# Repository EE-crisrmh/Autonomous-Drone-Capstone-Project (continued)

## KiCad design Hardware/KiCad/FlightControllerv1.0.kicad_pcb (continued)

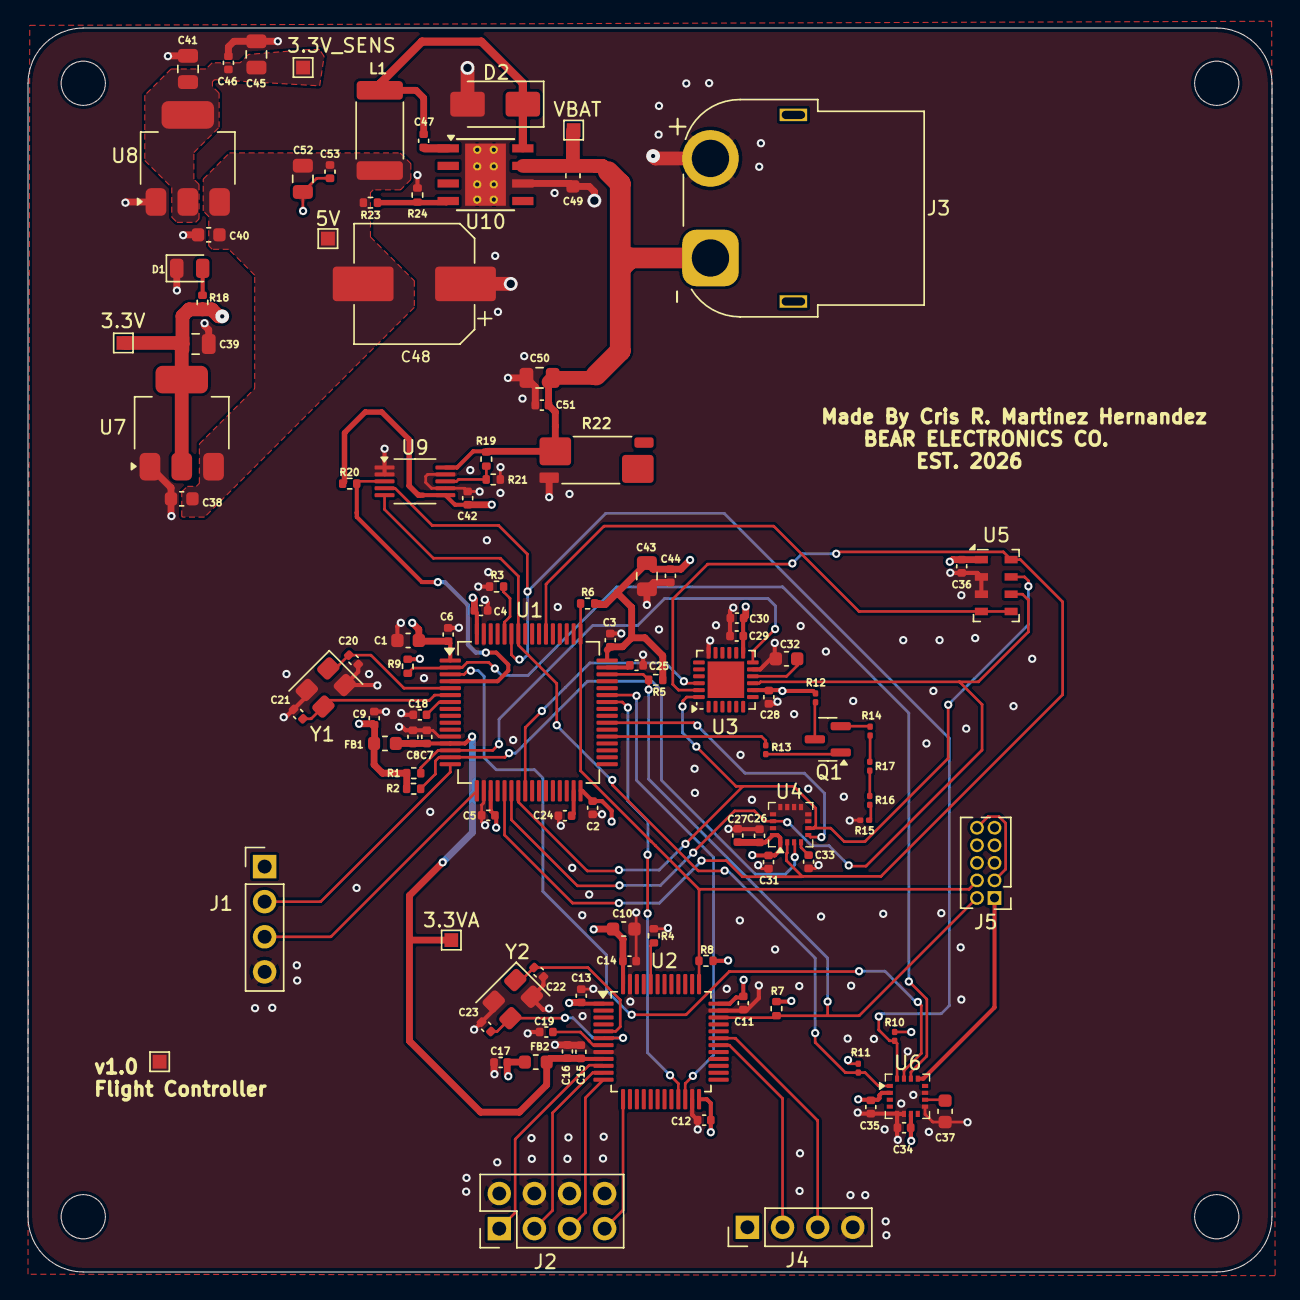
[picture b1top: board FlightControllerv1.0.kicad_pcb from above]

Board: 4 copper layers, 90.0 x 90.0 mm, 110 parts (0 on the bottom side), 57 nets.

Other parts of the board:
3.3VA: TestPoint; TestPoint_Pad_1.0x1.0mm
VBAT: TestPoint; TestPoint_Pad_1.0x1.0mm

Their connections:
+3.3VA: 3.3VA.1; also elsewhere on the board
VBAT: VBAT.1; also elsewhere on the board

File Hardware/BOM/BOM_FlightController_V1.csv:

,Reference designator,Value,Package,LCSC Part #,MPN,Manufacturer ,Description,Cost,
,"C24, C25, C27, C30 ",2.2 uF,402,C107369,CL05A225KP5NSNC,Samsung Electro-Mechanics,2.2uF 10V X5R ceramic cap,0.0042,
,"C1, C10, C38, C40, C49",10uF,603,C19702,CL10A106KP8NNNC,Samsung Electro-Mechanics,CAP CER 10uF 10V X5R 0603,0.0125,
,"C2, C3, C4, C5, C6, C7, C8, C11, C12, C13, C14, C15, C16, C18, C19, C26, C29, C33-C36, C42, C44, C46, C51, C53",100nF,402,C1525,CL05B104KO5NNNC,Samsung Electro-Mechanics,CAP CER 100nF 16V X7R 0402,0.16,
," C9, C17",1uF,402,C29266,CL05A105KO5NNNC,Samsung Electro-Mechanics,CAP CER 1uF 16V X5R 0402,0.35,
,"C20, C21, C22, C23",10pF,402,C32949,CL05C100JB5NNNC,Samsung Electro-Mechanics,CAP CER 10pF 50V C0G 0402,0.24,
,"C28, C31, C47",10nF,402,C15195,CL05B103KB5NNNC,Samsung Electro-Mechanics,CAP CER 10nF 50V X7R 0402,0.16,
,C32,0.47uF,603,C1623,CL10B474KA8NNNC,Samsung Electro-Mechanics,CAP CER 470nF 25V X7R 0603,0.74,
,C37,4.7uF,603,C19666,CL10A475KO8NNNC,Samsung Electro-Mechanics,CAP CER 4.7uF 16V X5R 0603,0.12,
," C39, C41",22uF,805,C5674,CL21A226MQQNNNE,Samsung Electro-Mechanics,CAP CER 22uF 6.3V X5R 0805,0.28,
,"C43, C45, C50, C52",47uF,805,C16780,CL21A476MQYNNNE,Samsung Electro-Mechanics,CAP CER 47uF 6.3V X5R 0805,0.56,
,C48,220uF,"SMD,D8xL10.5mm",C48935405,RVE35V220M8X10,JIERR,CAP ALUM 220uF ±20% 35V SMD,0.41,
,D1 ,RED,805,C19171391,YLED0805R,YONGYUTAI,LED RED 0805 SMD,0.82,
,D2,B340,SMA(DO-214AC),C908680,SS34,GOODWORK,DIODE SCHOTTKY 40V SMA(DO-214AC),0.53,
,"FB1, FB2",120 ohm,603,C14709,BLM18PG121SN1D,muRata,FERRITE BEAD 120Ω 0603 1LN,0.74,
,J1,connector,"Through Hole,P=2.54mm",C32713270,HX PZ2.54-1x4P ZZ,hanxia,CONN HEADER 4POS 2.54mm SINGLE ROW TH,0.13,
,J2,connector,"Through Hole,P=2.54mm",C32713277,HX PZ2.54-2x4P ZZ,hanxia,CONN HEADER 8POS 2.54mm DUAL ROW TH,0.6,
,J4,connector,"Through Hole,P=2.54mm",C32713270,HX PZ2.54-1x4P ZZ,hanxia,CONN HEADER 4POS 2.54mm SINGLE ROW TH,0.13,
,J5,connector,"Through Hole,P=1.27mm",C41426986,A127M01-0B10P51-H10A39,JXTCONN,CONN HEADER 10POS DUAL ROW TH,0.38,
,L1,15uH,"2512 SMD,7x6.6mm",C5349699,APH0630T150M,APV,"FIXED IND 15uH 3A 113mΩ SMD,7x6.6mm",0.4,
,Q1,20V 350mA NPN transistor,SOT-23,C916372,MMBT2222A,JSMSEMI,TRANS NPN 20V 350mA SOT-23,0.56,
,"R1, R2, R3, R4, R5, R6, R7, R8, R9, R19, R20, R23",10k,603,C2930027,FRC0603J103 TS,FOJAN,RES 10kΩ ±5% 100mW 0603,0.14,
,"R10, R11",4.7k,603,C99782,RC0603FR-074K7L,YAGEO,RES 4.7kΩ ±1% 100mW 0603,0.23,
,"R12, R13, R14, R15, R16, R17",1.8 ohm,603,C2907087,FRC0603J1R8 TS,FOJAN,RES 1.8Ω ±5% 100mW 0603,0.2,
,R18,1k,402,C852624,RT0402BRD071KL,YAGEO,RES 1kΩ ±0.1% 62.5mW 0402,1,
,R21,3.3k,402,C482167,CRCW04023K30FKED,VISHAY,RES 3.3kΩ ±1% 63mW 0402,0.4,
,R22,2m,2512,C2994640,HoLLR2512-3W-2mR-1%,Milliohm,RES 2mΩ ±1% 3W 2512,0.33,
,R24,3.24k,402,C3972407,CRCW04023K24FKED,VISHAY,RES 3.24kΩ ±1% 62.5mW 0402,0.42,
,U1,STM32F405RGTx,LQFP-64(10x10),C1337199,STM32F405RGT7,ST,Arm Cortex - M4 32b,12.83,
,U2,STM32F103C8Tx,LQFP-48(7x7),C8734,STM32F103C8T6,ST,Arm-Based 32b ,1.44,
,U3,ICM-20689,QFN-24-EP(4x4),C2649494,ICM-20689,TDK InvenSense,6-axis MEMS motion tracking,16.5,
,U4,ICM-20602,LGA-16(3x3),C97633,ICM-20602,TDK InvenSense,6-Axis MEMS motion tracking ,16.5,Not available rn
,U5,MS5611-01BA,QFN-8(3x5),C15639,MS561101BA03-50,TE Connectivity,Barometric preassure sensor,7.11,Not available rn
,U6,IST8310,LGA-16(3x3),C2683055,IST8310,iSentek,3D Magnetometer,5.63,"U5 MS5611 footprint may have minor QFN vs LGA package discrepancy, please verify pad alignment."
,"U7, U8",AMS1117-3.3,SOT-223,C5205141,AMS1117-3.3V,JSMSEMI,800mA Bipolar Linear Regulator,0.4,
,U9,INA226,VSOP-10,C49851,INA226AIDGSR,TI,Bi-Directional CURRENT/POWER MONITOR with I2C Interface,0.79,
,U10,TPS5430DDA,SOIC-8-EP,C9864,TPS5430DDAR,TI,"3-A, Wide Input Range, Step-Down Converter",0.81,
,"Y1, Y2",16MHz,SMD3225-4P,C13738,X322516MLB4SI,YXC Crystal Oscillators,CRYSTAL 16MHz 9pF SMD,0.49,
,J3,connector ,AMASS XT60PW-F 1x02 P7.20mm Horizontal,C428722,XT60PW-F,Changzhou Amass Elec,Power Connectors ,0.64,
,,,,,,,,,

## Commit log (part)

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2026-04-11 Remove testing message from README
